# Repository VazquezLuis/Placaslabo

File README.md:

# Placaslabo
Repositorio de PCBs hechos para el labo

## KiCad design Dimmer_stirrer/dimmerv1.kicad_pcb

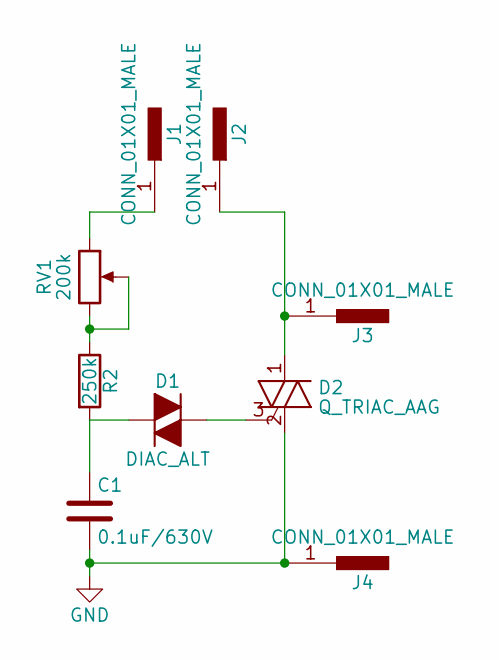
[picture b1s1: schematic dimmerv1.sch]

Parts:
C1: 0.1uF/630V; C_Rect_L18.0mm_W5.0mm_P15.00mm_FKS3_FKP3
D1: DIAC_ALT; D_DO-35_SOD27_P7.62mm_Horizontal
D2: Q_TRIAC_AAG; TO-220_Vertical
J1, J2, J3, J4: CONN_01X01_MALE; Pin_Header_Straight_1x01_Pitch2.54mm
R2: 250k; R_Axial_DIN0207_L6.3mm_D2.5mm_P10.16mm_Horizontal
RV1: 200k; Potentiometer_Alps_RK163_Single_Vertical

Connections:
GND: C1.2, D2.2 (A2), J4.1
unnamed: C1.1, D1.1 (K), R2.2
unnamed: D1.2 (A), D2.3 (G)
unnamed: D2.1 (A1), J2.1, J3.1
unnamed: J1.1, RV1.1
unnamed: R2.1, RV1.2, RV1.3

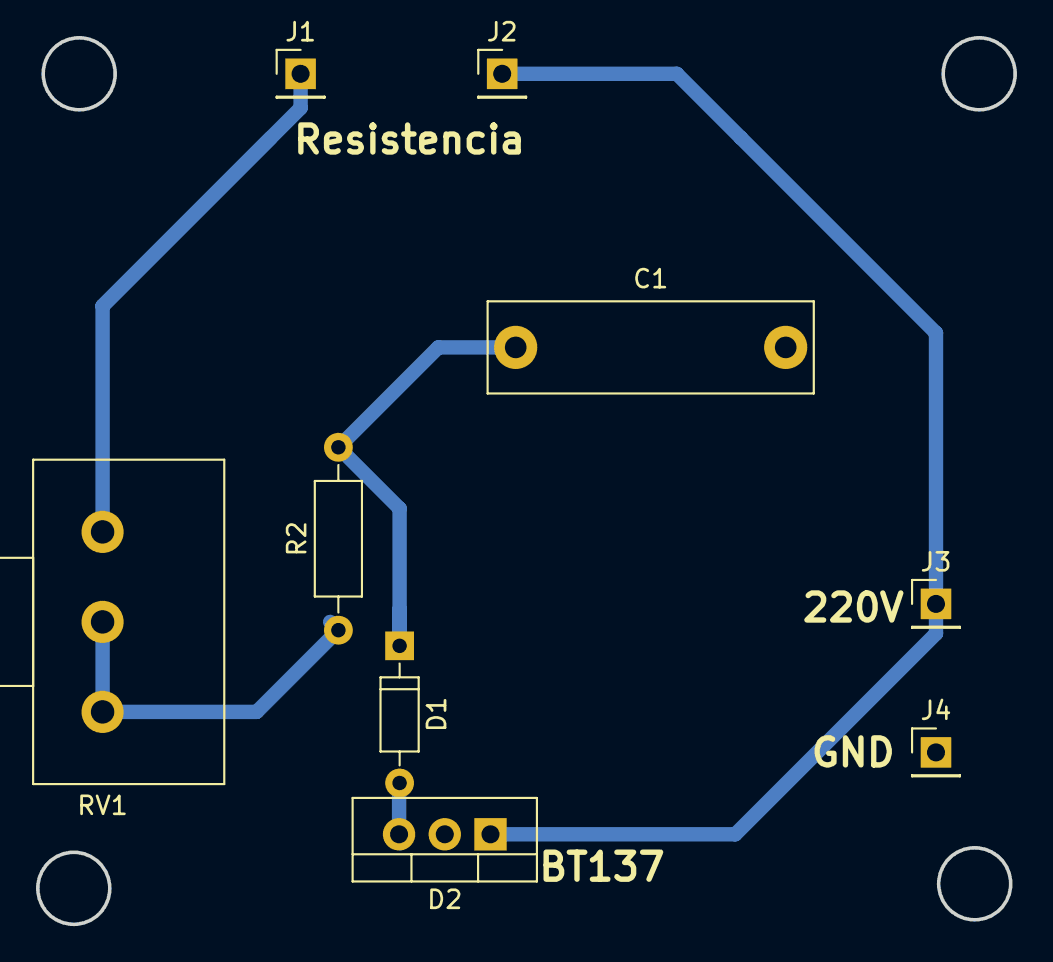
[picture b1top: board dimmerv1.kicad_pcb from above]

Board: 2 copper layers, 54.3 x 49.2 mm, 9 parts (0 on the bottom side), 6 nets.

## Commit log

2017-09-15 Agregado PCB del dimmer
